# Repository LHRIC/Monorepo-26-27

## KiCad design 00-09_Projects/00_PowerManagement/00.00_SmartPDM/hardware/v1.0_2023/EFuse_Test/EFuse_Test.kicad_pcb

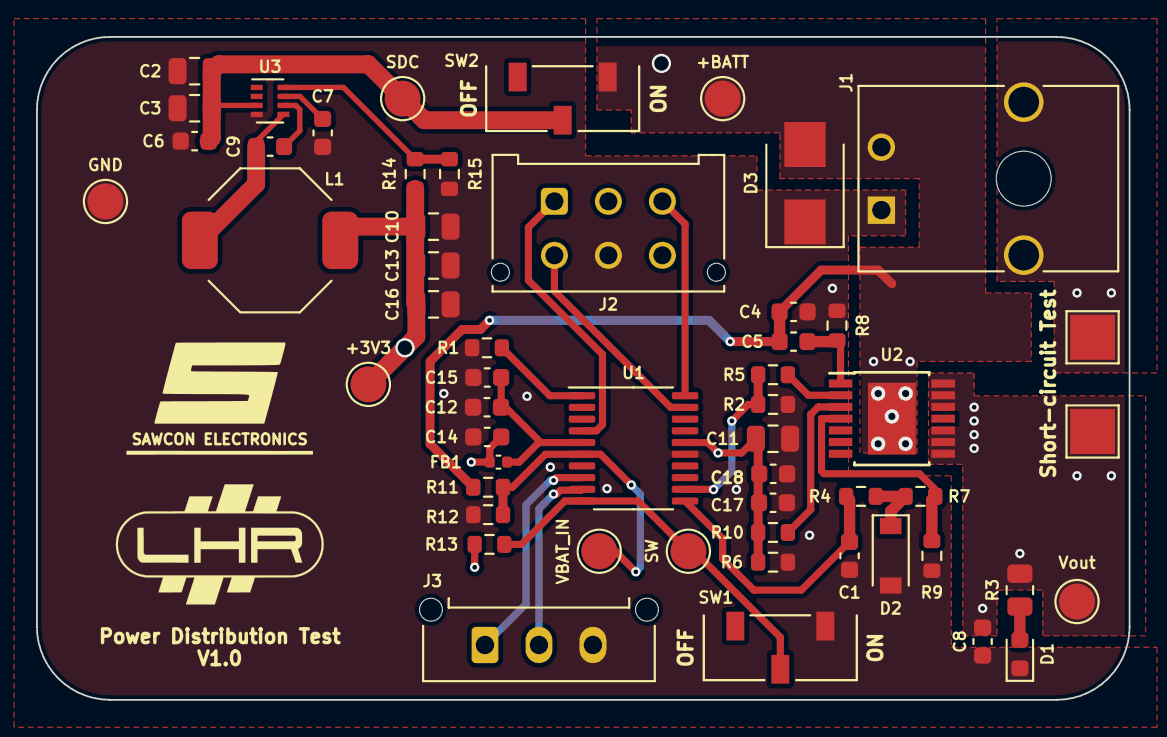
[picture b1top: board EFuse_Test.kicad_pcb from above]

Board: 4 copper layers, 60.7 x 36.8 mm, 53 parts (0 on the bottom side), 26 nets.

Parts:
C1: 220pF; C_0603_1608Metric
C2, C3: 4.7uF; C_0805_2012Metric
C4, C6, C9, C12, C14, C17, C18: .1uF; C_0603_1608Metric
C5: 47nF; C_0603_1608Metric
C7: 33nF; C_0603_1608Metric
C8: 10nF; C_0603_1608Metric
C10, C13, C16: 22uF; C_0805_2012Metric
C11: 10uF; C_0805_2012Metric
C15: 1uF; C_0603_1608Metric
D1: LED; LED_0603_1608Metric
D2: 3.3V; D_SOD-123
D3: 33.2v; D_SMB
FB1: 100 @ 100MHz; C_0402_1005Metric
J1: Conn_01x04; 1723103102
J2: Conn_02x03_Odd_Even; Molex_Micro-Fit_3.0_43045-0612_2x03_P3.00mm_Vertical
J3: Conn_01x03; Molex_Micro-Fit_3.0_43650-0315_1x03_P3.00mm_Vertical
L1: 4.7uH; SRU8043-4R7Y
R1, R2, R6, R13, R15: 10k; R_0603_1608Metric
R3: 1k; R_0805_2012Metric
R4, R5, R7, R10: 4.7k; R_0603_1608Metric
R8: 47; R_0603_1608Metric
R9: 4.42k; R_0603_1608Metric
R11: 16k; R_0603_1608Metric
R12: 3.9k; R_0603_1608Metric
R14: 30.9k; R_0603_1608Metric
SW1, SW2: SW_SPST; SW_JS102011JCQN
TP1, TP2, TP3, TP4, TP5, TP6, TP7: TP; TestPoint_Pad_D2.0mm
U1: STM32F030F4P6TR; TSSOP-20_4.4x6.5mm_P0.65mm
U2: BTS7006-1EPZ; Infineon_PG-TSDSO-14-22
U3: TPS62933; SOT-583

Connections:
+3.3VA: C12.1, C15.1, FB1.2, U1.5 (VDDA)
+3V3: C10.1, C11.1, C13.1, C14.1, C16.1, C17.1, C18.1, FB1.1, J2.2, L1.2, R6.2, R10.2, R13.2, R14.1, TP6.1, U1.16 (VDD)
+BATT: C4.1, C5.1, D3.2 (A2), J1.2, R11.1, SW2.1 (A), TP7.1, U2.15 (VS)
CS: C1.1, R4.1, U1.11 (PA5)
EN: R2.2, R5.2, U1.12 (PA6)
GND: C1.2, C2.2, C3.2, C4.2, C6.2, C7.2, C8.2, C10.2, C11.2, C12.2, C13.2, C14.2, C15.2, C16.2, C17.2, C18.2, D1.1 (K), D2.2 (A), D3.1 (A1), J1.1, J1.3, J1.4, J2.5, J3.3, R1.1, R2.1, R6.1, R8.1, R9.2, R12.2, R15.2, SW1.1 (A), TP2.1, U1.15 (VSS), U3.4 (GND)
NRST: J2.1, U1.4 (NRST)
unnamed: C5.2, R8.2, U2.1 (GND)
unnamed: C7.1, U3.7 (SS)
unnamed: C9.1, L1.1, U3.5 (SW)
unnamed: C9.2, U3.6 (BST)
unnamed: D1.2 (A), R3.2
unnamed: D2.1 (K), R4.2, R7.1
unnamed: R1.2, U1.1 (BOOT0)
unnamed: R5.1, U2.2 (IN)
unnamed: R7.2, R9.1, U2.4 (IS)
unnamed: R10.1, U2.3 (DEN)
unnamed: R14.2, R15.1, U3.8 (FB)
SDC: C2.1, C3.1, C6.1, SW2.2 (B), TP1.1, U3.3 (VIN)
SW: R13.1, SW1.2 (B), TP5.1, U1.10 (PA4)
SWCLK: J2.3, U1.20 (PA14)
SWDIO: J2.4, U1.19 (PA13)
UART_RX: J3.2, U1.9 (PA3)
UART_TX: J3.1, U1.8 (PA2)
VBAT_IN: R11.2, R12.1, TP4.1, U1.6 (PA0)
Vout: C8.1, R3.1, TP3.1, U2.8 (OUT), U2.9 (OUT), U2.10 (OUT), U2.12 (OUT), U2.13 (OUT), U2.14 (OUT)

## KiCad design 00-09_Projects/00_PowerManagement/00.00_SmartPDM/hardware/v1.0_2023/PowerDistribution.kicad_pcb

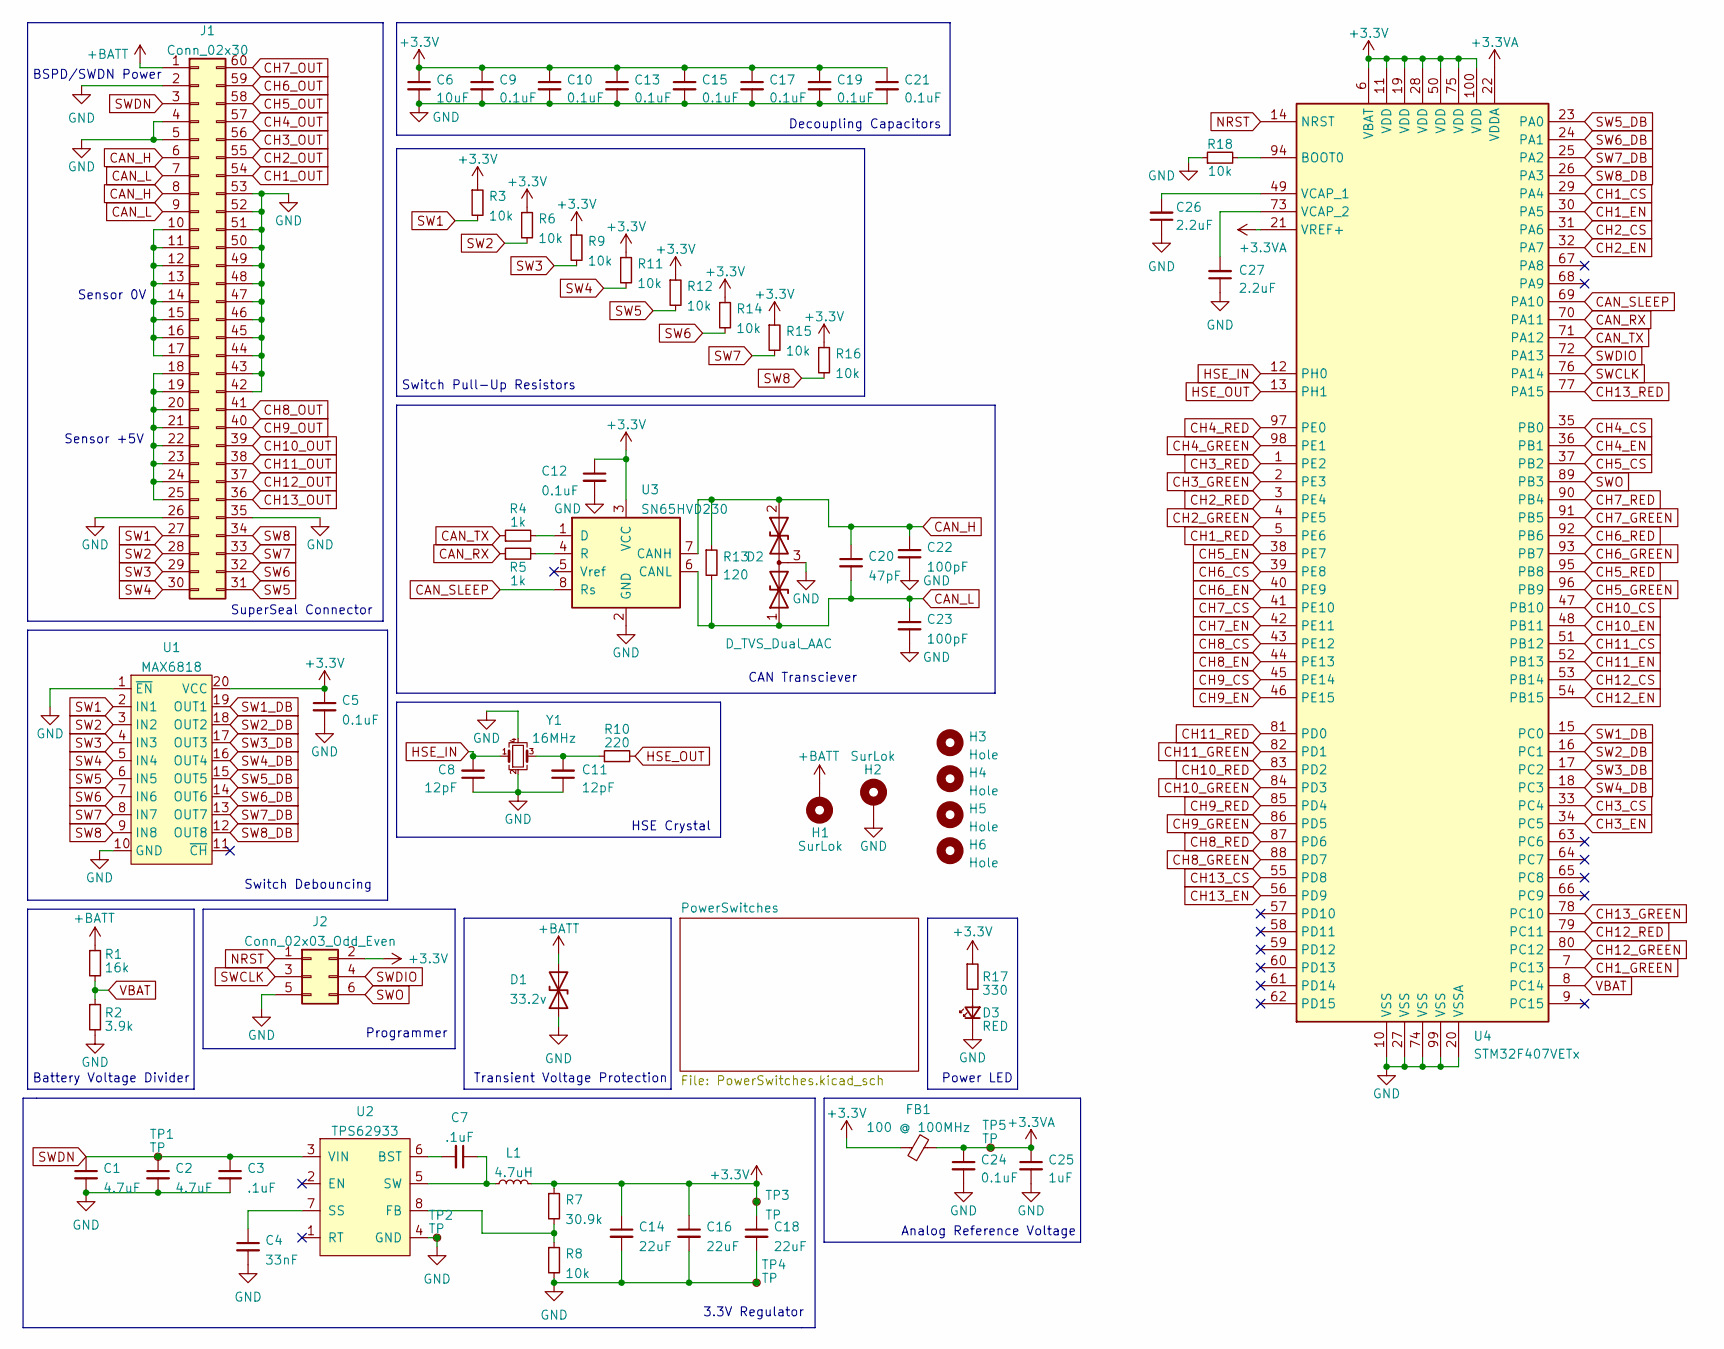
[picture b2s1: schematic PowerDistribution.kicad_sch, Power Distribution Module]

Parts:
C1, C2: 4.7uF; C_0805_2012Metric
C3, C7: .1uF; C_0603_1608Metric
C4: 33nF; C_0603_1608Metric
C5, C9, C10, C12, C13, C15, C17, C19, C21, C24: 0.1uF; C_0603_1608Metric
C6: 10uF; C_0805_2012Metric
C8, C11: 12pF; C_0402_1005Metric
C14, C16, C18: 22uF; C_0805_2012Metric
C20: 47pF; C_0402_1005Metric
C22, C23: 100pF; C_0603_1608Metric
C25: 1uF; C_0603_1608Metric
C26, C27: 2.2uF; C_0603_1608Metric
D1: 33.2v; D_SMB
D2: D_TVS_Dual_AAC; SOT-23
D3: RED; LED_0603_1608Metric
FB1: 100 @ 100MHz; C_0402_1005Metric
H1, H2: SurLok; SurLok_5.7
H3, H4, H5, H6: Hole; MountingHole_3.2mm_M3
J1: Conn_02x30; TE_6473427-1
J2: Conn_02x03_Odd_Even; Molex_Micro-Fit_3.0_43045-0612_2x03_P3.00mm_Vertical
L1: 4.7uH; SRU8043-4R7Y
R1: 16k; R_0603_1608Metric
R2: 3.9k; R_0603_1608Metric
R3, R6, R8, R9, R11, R12, R14, R15, R16, R18: 10k; R_0603_1608Metric
R4, R5: 1k; R_0603_1608Metric
R7: 30.9k; R_0603_1608Metric
R10: 220; R_0603_1608Metric
R13: 120; R_0603_1608Metric
R17: 330; R_0603_1608Metric
TP1, TP2, TP3, TP4, TP5: TP; TestPoint_Pad_D2.0mm
U1: MAX6818; SSOP-20_5.3x7.2mm_P0.65mm
U2: TPS62933; SOT-583
U3: SN65HVD230; SOIC-8_3.9x4.9mm_P1.27mm
U4: STM32F407VETx; LQFP-100_14x14mm_P0.5mm
Y1: 16MHz; Crystal_SMD_3225-4Pin_3.2x2.5mm

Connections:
+3.3VA: C24.1, C25.1, FB1.2, TP5.1, U4.21 (VREF+), U4.22 (VDDA)
+3V3: C5.1, C6.1, C9.1, C10.1, C12.1, C13.1, C14.1, C15.1, C16.1, C17.1, C18.1, C19.1, C21.1, FB1.1, J2.2, L1.2, R3.1, R6.1, R7.1, R9.1, R11.1, R12.1, R14.1, R15.1, R16.1, R17.1, TP3.1, U1.20 (VCC), U3.3 (VCC), U4.6 (VBAT), U4.11 (VDD), U4.19 (VDD), U4.28 (VDD), U4.50 (VDD), U4.75 (VDD), U4.100 (VDD); also elsewhere on the board
+BATT: D1.2 (A2), H1.1, J1.1, R1.1; also elsewhere on the board
CAN_H: C20.1, C22.1, D2.2 (A2), J1.6, J1.8, R13.1, U3.7 (CANH)
CAN_L: C20.2, C23.1, D2.1 (A1), J1.7, J1.9, R13.2, U3.6 (CANL)
CAN_RX: R5.1, U4.70 (PA11)
CAN_SLEEP: U3.8 (Rs), U4.69 (PA10)
CAN_TX: R4.1, U4.71 (PA12)
CH1_CS: U4.29 (PA4); also elsewhere on the board
CH1_EN: U4.30 (PA5); also elsewhere on the board
CH1_GREEN: U4.7 (PC13); also elsewhere on the board
CH1_OUT: J1.54; also elsewhere on the board
CH1_RED: U4.5 (PE6); also elsewhere on the board
CH2_CS: U4.31 (PA6); also elsewhere on the board
CH2_EN: U4.32 (PA7); also elsewhere on the board
CH2_GREEN: U4.4 (PE5); also elsewhere on the board
CH2_OUT: J1.55; also elsewhere on the board
CH2_RED: U4.3 (PE4); also elsewhere on the board
CH3_CS: U4.33 (PC4); also elsewhere on the board
CH3_EN: U4.34 (PC5); also elsewhere on the board
CH3_GREEN: U4.2 (PE3); also elsewhere on the board
CH3_OUT: J1.56; also elsewhere on the board
CH3_RED: U4.1 (PE2); also elsewhere on the board
CH4_CS: U4.35 (PB0); also elsewhere on the board
CH4_EN: U4.36 (PB1); also elsewhere on the board
CH4_GREEN: U4.98 (PE1); also elsewhere on the board
CH4_OUT: J1.57; also elsewhere on the board
CH4_RED: U4.97 (PE0); also elsewhere on the board
CH5_CS: U4.37 (PB2); also elsewhere on the board
CH5_EN: U4.38 (PE7); also elsewhere on the board
CH5_GREEN: U4.96 (PB9); also elsewhere on the board
CH5_OUT: J1.58; also elsewhere on the board
CH5_RED: U4.95 (PB8); also elsewhere on the board
CH6_CS: U4.39 (PE8); also elsewhere on the board
CH6_EN: U4.40 (PE9); also elsewhere on the board
CH6_GREEN: U4.93 (PB7); also elsewhere on the board
CH6_OUT: J1.59; also elsewhere on the board
CH6_RED: U4.92 (PB6); also elsewhere on the board
CH7_CS: U4.41 (PE10); also elsewhere on the board
CH7_EN: U4.42 (PE11); also elsewhere on the board
CH7_GREEN: U4.91 (PB5); also elsewhere on the board
CH7_OUT: J1.60; also elsewhere on the board
CH7_RED: U4.90 (PB4); also elsewhere on the board
CH8_CS: U4.43 (PE12); also elsewhere on the board
CH8_EN: U4.44 (PE13); also elsewhere on the board
CH8_GREEN: U4.88 (PD7); also elsewhere on the board
CH8_OUT: J1.41; also elsewhere on the board
CH8_RED: U4.87 (PD6); also elsewhere on the board
CH9_CS: U4.45 (PE14); also elsewhere on the board
CH9_EN: U4.46 (PE15); also elsewhere on the board
CH9_GREEN: U4.86 (PD5); also elsewhere on the board
CH9_OUT: J1.40; also elsewhere on the board
CH9_RED: U4.85 (PD4); also elsewhere on the board
CH10_CS: U4.47 (PB10); also elsewhere on the board
CH10_EN: U4.48 (PB11); also elsewhere on the board
CH10_GREEN: U4.84 (PD3); also elsewhere on the board
CH10_OUT: J1.39; also elsewhere on the board
CH10_RED: U4.83 (PD2); also elsewhere on the board
CH11_CS: U4.51 (PB12); also elsewhere on the board
CH11_EN: U4.52 (PB13); also elsewhere on the board
CH11_GREEN: U4.82 (PD1); also elsewhere on the board
CH11_OUT: J1.38; also elsewhere on the board
CH11_RED: U4.81 (PD0); also elsewhere on the board
CH12_CS: U4.53 (PB14); also elsewhere on the board
CH12_EN: U4.54 (PB15); also elsewhere on the board
CH12_GREEN: U4.80 (PC12); also elsewhere on the board
CH12_OUT: J1.37; also elsewhere on the board
CH12_RED: U4.79 (PC11); also elsewhere on the board
CH13_CS: U4.55 (PD8); also elsewhere on the board
CH13_EN: U4.56 (PD9); also elsewhere on the board
CH13_GREEN: U4.78 (PC10); also elsewhere on the board
CH13_OUT: J1.36; also elsewhere on the board
CH13_RED: U4.77 (PA15); also elsewhere on the board
GND: C1.2, C2.2, C3.2, C4.2, C5.2, C6.2, C8.1, C9.2, C10.2, C11.1, C12.2, C13.2, C14.2, C15.2, C16.2, C17.2, C18.2, C19.2, C21.2, C22.2, C23.2, C24.2, C25.2, C26.1, C27.1, D1.1 (A1), D2.3 (common), D3.1 (K), H2.1, J1.2, J1.4, J1.5, J1.26, J1.35, J1.42, J1.43, J1.44, J1.45, J1.46, J1.47, J1.48, J1.49, J1.50, J1.51, J1.52, J1.53, J2.5, R2.2, R8.2, R18.1, TP2.1, TP4.1, U1.1 (~EN), U1.10 (GND), U2.4 (GND), U3.2 (GND), U4.10 (VSS), U4.20 (VSSA), U4.27 (VSS), U4.74 (VSS), U4.99 (VSS), Y1.2, Y1.4; also elsewhere on the board
HSE_IN: C8.2, U4.12 (PH0), Y1.1
HSE_OUT: R10.2, U4.13 (PH1)
NRST: J2.1, U4.14 (NRST)
unnamed: C4.1, U2.7 (SS)
unnamed: C7.1, L1.1, U2.5 (SW)
unnamed: C7.2, U2.6 (BST)
unnamed: C11.2, R10.1, Y1.3
unnamed: C26.2, U4.49 (VCAP_1)
unnamed: C27.2, U4.73 (VCAP_2)
unnamed: D3.2 (A), R17.2
unnamed: J1.10, J1.11, J1.12, J1.13, J1.14, J1.15, J1.16, J1.17
unnamed: J1.18, J1.19, J1.20, J1.21, J1.22, J1.23, J1.24, J1.25
unnamed: R4.2, U3.1 (D)
unnamed: R5.2, U3.4 (R)
unnamed: R7.2, R8.1, U2.8 (FB)
unnamed: R18.2, U4.94 (BOOT0)
SW1: J1.27, R3.2, U1.2 (IN1)
SW1_DB: U1.19 (OUT1), U4.15 (PC0)
SW2: J1.28, R6.2, U1.3 (IN2)
SW2_DB: U1.18 (OUT2), U4.16 (PC1)
SW3: J1.29, R9.2, U1.4 (IN3)
SW3_DB: U1.17 (OUT3), U4.17 (PC2)
SW4: J1.30, R11.2, U1.5 (IN4)
SW4_DB: U1.16 (OUT4), U4.18 (PC3)
SW5: J1.31, R12.2, U1.6 (IN5)
SW5_DB: U1.15 (OUT5), U4.23 (PA0)
SW6: J1.32, R14.2, U1.7 (IN6)
SW6_DB: U1.14 (OUT6), U4.24 (PA1)
SW7: J1.33, R15.2, U1.8 (IN7)
SW7_DB: U1.13 (OUT7), U4.25 (PA2)
SW8: J1.34, R16.2, U1.9 (IN8)
SW8_DB: U1.12 (OUT8), U4.26 (PA3)
SWCLK: J2.3, U4.76 (PA14)
SWDIO: J2.4, U4.72 (PA13)
SWDN: C1.1, C2.1, C3.1, J1.3, TP1.1, U2.3 (VIN)
SWO: J2.6, U4.89 (PB3)
VBAT: R1.2, R2.1, U4.8 (PC14)

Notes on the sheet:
Decoupling Capacitors
SuperSeal Connector
Switch Debouncing
Analog Reference Voltage
Power LED
Programmer
CAN Transciever
Sensor +5V
Sensor 0V
Transient Voltage Protection
3.3V Regulator
Battery Voltage Divider
HSE Crystal
BSPD/SWDN Power
Switch Pull-Up Resistors

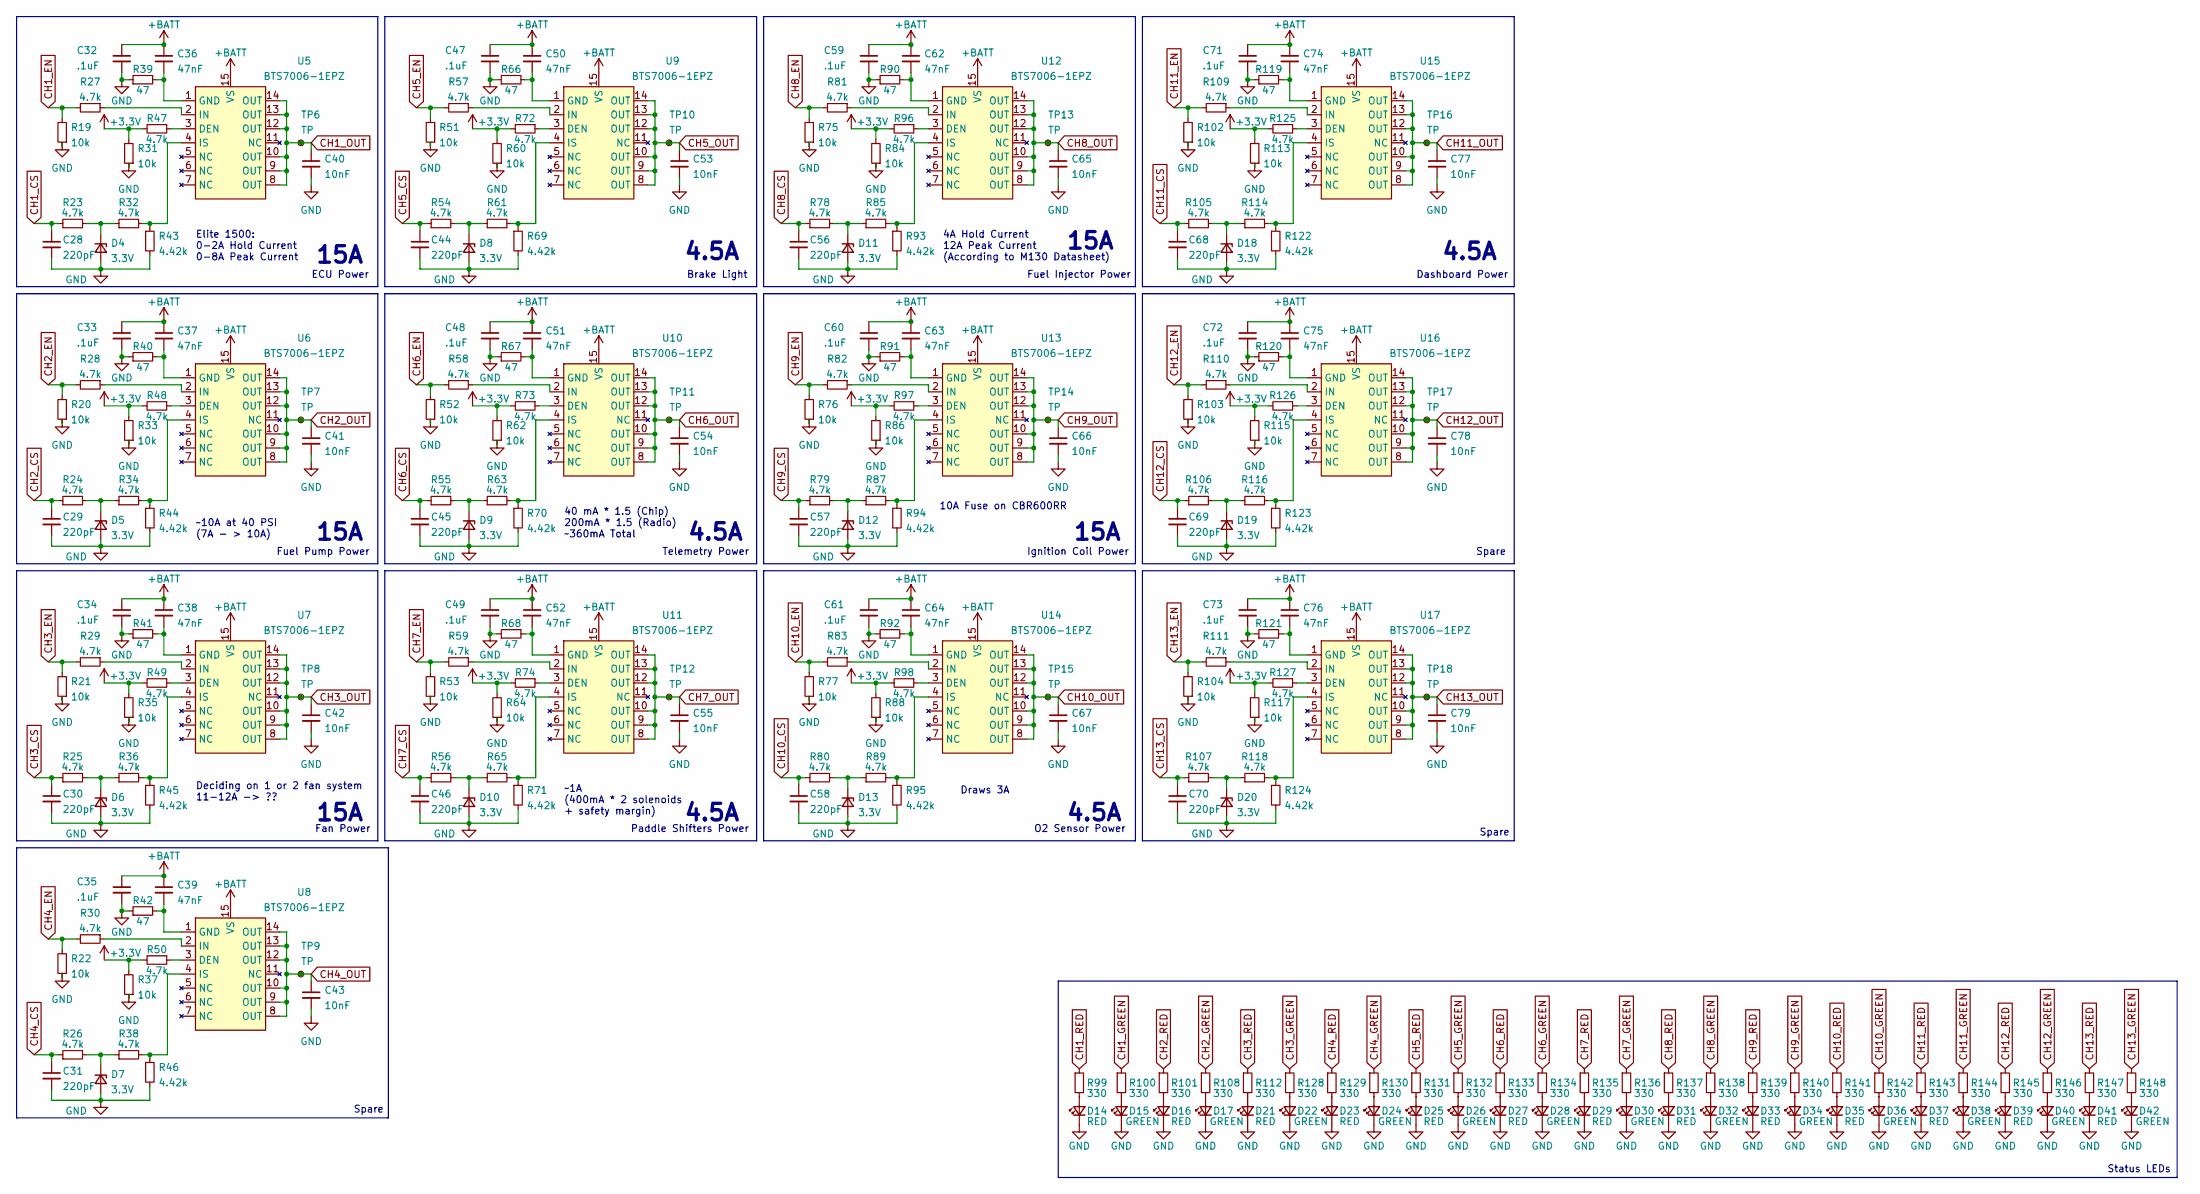
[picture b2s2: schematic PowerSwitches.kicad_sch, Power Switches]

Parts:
C28, C29, C30, C31, C44, C45, C46, C56, C57, C58, C68, C69, C70: 220pF; C_0603_1608Metric
C32, C33, C34, C35, C47, C48, C49, C59, C60, C61, C71, C72, C73: .1uF; C_0603_1608Metric
C36, C37, C38, C39, C50, C51, C52, C62, C63, C64, C74, C75, C76: 47nF; C_0603_1608Metric
C40, C41, C42, C43, C53, C54, C55, C65, C66, C67, C77, C78, C79: 10nF; C_0603_1608Metric
D4, D5, D6, D7, D8, D9, D10, D11, D12, D13, D18, D19, D20: 3.3V; D_SOD-123
D14, D16, D21, D23, D25, D27, D29, D31, D33, D35, D37, D39, D41: RED; LED_0603_1608Metric
D15, D17, D22, D24, D26, D28, D30, D32, D34, D36, D38, D40, D42: GREEN; LED_0603_1608Metric
R19, R20, R21, R22, R31, R33, R35, R37, R51, R52, R53, R60, R62, R64, R75, R76, R77, R84, R86, R88, R102, R103, R104, R113, R115, R117: 10k; R_0603_1608Metric
R23, R24, R25, R26, R27, R28, R29, R30, R32, R34, R36, R38, R47, R48, R49, R50, R54, R55, R56, R57, R58, R59, R61, R63, R65, R72, R73, R74, R78, R79, R80, R81, R82, R83, R85, R87, R89, R96, R97, R98, R105, R106, R107, R109, R110, R111, R114, R116, R118, R125, R126, R127: 4.7k; R_0603_1608Metric
R39, R40, R41, R42, R66, R67, R68, R90, R91, R92, R119, R120, R121: 47; R_0603_1608Metric
R43, R44, R45, R46, R69, R70, R71, R93, R94, R95, R122, R123, R124: 4.42k; R_0603_1608Metric
R99, R100, R101, R108, R112, R128, R129, R130, R131, R132, R133, R134, R135, R136, R137, R138, R139, R140, R141, R142, R143, R144, R145, R146, R147, R148: 330; R_0603_1608Metric
TP6, TP7, TP8, TP9, TP10, TP11, TP12, TP13, TP14, TP15, TP16, TP17, TP18: TP; TestPoint_Pad_D2.0mm
U5, U6, U7, U8, U9, U10, U11, U12, U13, U14, U15, U16, U17: BTS7006-1EPZ; Infineon_PG-TSDSO-14-22

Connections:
+3V3: R31.2, R33.2, R35.2, R37.2, R47.2, R48.2, R49.2, R50.2, R60.2, R62.2, R64.2, R72.2, R73.2, R74.2, R84.2, R86.2, R88.2, R96.2, R97.2, R98.2, R113.2, R115.2, R117.2, R125.2, R126.2, R127.2; also elsewhere on the board
+BATT: C32.1, C33.1, C34.1, C35.1, C36.1, C37.1, C38.1, C39.1, C47.1, C48.1, C49.1, C50.1, C51.1, C52.1, C59.1, C60.1, C61.1, C62.1, C63.1, C64.1, C71.1, C72.1, C73.1, C74.1, C75.1, C76.1, U5.15 (VS), U6.15 (VS), U7.15 (VS), U8.15 (VS), U9.15 (VS), U10.15 (VS), U11.15 (VS), U12.15 (VS), U13.15 (VS), U14.15 (VS), U15.15 (VS), U16.15 (VS), U17.15 (VS); also elsewhere on the board
CH1_CS: C28.1, R23.1; also elsewhere on the board
CH1_EN: R19.2, R27.2; also elsewhere on the board
CH1_GREEN: R100.1; also elsewhere on the board
CH1_OUT: C40.1, TP6.1, U5.8 (OUT), U5.9 (OUT), U5.10 (OUT), U5.12 (OUT), U5.13 (OUT), U5.14 (OUT); also elsewhere on the board
CH1_RED: R99.1; also elsewhere on the board
CH2_CS: C29.1, R24.1; also elsewhere on the board
CH2_EN: R20.2, R28.2; also elsewhere on the board
CH2_GREEN: R108.1; also elsewhere on the board
CH2_OUT: C41.1, TP7.1, U6.8 (OUT), U6.9 (OUT), U6.10 (OUT), U6.12 (OUT), U6.13 (OUT), U6.14 (OUT); also elsewhere on the board
CH2_RED: R101.1; also elsewhere on the board
CH3_CS: C30.1, R25.1; also elsewhere on the board
CH3_EN: R21.2, R29.2; also elsewhere on the board
CH3_GREEN: R128.1; also elsewhere on the board
CH3_OUT: C42.1, TP8.1, U7.8 (OUT), U7.9 (OUT), U7.10 (OUT), U7.12 (OUT), U7.13 (OUT), U7.14 (OUT); also elsewhere on the board
CH3_RED: R112.1; also elsewhere on the board
CH4_CS: C31.1, R26.1; also elsewhere on the board
CH4_EN: R22.2, R30.2; also elsewhere on the board
CH4_GREEN: R130.1; also elsewhere on the board
CH4_OUT: C43.1, TP9.1, U8.8 (OUT), U8.9 (OUT), U8.10 (OUT), U8.12 (OUT), U8.13 (OUT), U8.14 (OUT); also elsewhere on the board
CH4_RED: R129.1; also elsewhere on the board
CH5_CS: C44.1, R54.1; also elsewhere on the board
CH5_EN: R51.2, R57.2; also elsewhere on the board
CH5_GREEN: R132.1; also elsewhere on the board
CH5_OUT: C53.1, TP10.1, U9.8 (OUT), U9.9 (OUT), U9.10 (OUT), U9.12 (OUT), U9.13 (OUT), U9.14 (OUT); also elsewhere on the board
CH5_RED: R131.1; also elsewhere on the board
CH6_CS: C45.1, R55.1; also elsewhere on the board
CH6_EN: R52.2, R58.2; also elsewhere on the board
CH6_GREEN: R134.1; also elsewhere on the board
CH6_OUT: C54.1, TP11.1, U10.8 (OUT), U10.9 (OUT), U10.10 (OUT), U10.12 (OUT), U10.13 (OUT), U10.14 (OUT); also elsewhere on the board
CH6_RED: R133.1; also elsewhere on the board
CH7_CS: C46.1, R56.1; also elsewhere on the board
CH7_EN: R53.2, R59.2; also elsewhere on the board
CH7_GREEN: R136.1; also elsewhere on the board
CH7_OUT: C55.1, TP12.1, U11.8 (OUT), U11.9 (OUT), U11.10 (OUT), U11.12 (OUT), U11.13 (OUT), U11.14 (OUT); also elsewhere on the board
CH7_RED: R135.1; also elsewhere on the board
CH8_CS: C56.1, R78.1; also elsewhere on the board
CH8_EN: R75.2, R81.2; also elsewhere on the board
CH8_GREEN: R138.1; also elsewhere on the board
CH8_OUT: C65.1, TP13.1, U12.8 (OUT), U12.9 (OUT), U12.10 (OUT), U12.12 (OUT), U12.13 (OUT), U12.14 (OUT); also elsewhere on the board
CH8_RED: R137.1; also elsewhere on the board
CH9_CS: C57.1, R79.1; also elsewhere on the board
CH9_EN: R76.2, R82.2; also elsewhere on the board
CH9_GREEN: R140.1; also elsewhere on the board
CH9_OUT: C66.1, TP14.1, U13.8 (OUT), U13.9 (OUT), U13.10 (OUT), U13.12 (OUT), U13.13 (OUT), U13.14 (OUT); also elsewhere on the board
CH9_RED: R139.1; also elsewhere on the board
CH10_CS: C58.1, R80.1; also elsewhere on the board
CH10_EN: R77.2, R83.2; also elsewhere on the board
CH10_GREEN: R142.1; also elsewhere on the board
CH10_OUT: C67.1, TP15.1, U14.8 (OUT), U14.9 (OUT), U14.10 (OUT), U14.12 (OUT), U14.13 (OUT), U14.14 (OUT); also elsewhere on the board
CH10_RED: R141.1; also elsewhere on the board
CH11_CS: C68.1, R105.1; also elsewhere on the board
CH11_EN: R102.2, R109.2; also elsewhere on the board
CH11_GREEN: R144.1; also elsewhere on the board
CH11_OUT: C77.1, TP16.1, U15.8 (OUT), U15.9 (OUT), U15.10 (OUT), U15.12 (OUT), U15.13 (OUT), U15.14 (OUT); also elsewhere on the board
CH11_RED: R143.1; also elsewhere on the board
CH12_CS: C69.1, R106.1; also elsewhere on the board
CH12_EN: R103.2, R110.2; also elsewhere on the board
CH12_GREEN: R146.1; also elsewhere on the board
CH12_OUT: C78.1, TP17.1, U16.8 (OUT), U16.9 (OUT), U16.10 (OUT), U16.12 (OUT), U16.13 (OUT), U16.14 (OUT); also elsewhere on the board
CH12_RED: R145.1; also elsewhere on the board
CH13_CS: C70.1, R107.1; also elsewhere on the board
CH13_EN: R104.2, R111.2; also elsewhere on the board
CH13_GREEN: R148.1; also elsewhere on the board
CH13_OUT: C79.1, TP18.1, U17.8 (OUT), U17.9 (OUT), U17.10 (OUT), U17.12 (OUT), U17.13 (OUT), U17.14 (OUT); also elsewhere on the board
CH13_RED: R147.1; also elsewhere on the board
GND: C28.2, C29.2, C30.2, C31.2, C32.2, C33.2, C34.2, C35.2, C40.2, C41.2, C42.2, C43.2, C44.2, C45.2, C46.2, C47.2, C48.2, C49.2, C53.2, C54.2, C55.2, C56.2, C57.2, C58.2, C59.2, C60.2, C61.2, C65.2, C66.2, C67.2, C68.2, C69.2, C70.2, C71.2, C72.2, C73.2, C77.2, C78.2, C79.2, D4.2 (A), D5.2 (A), D6.2 (A), D7.2 (A), D8.2 (A), D9.2 (A), D10.2 (A), D11.2 (A), D12.2 (A), D13.2 (A), D14.1 (K), D15.1 (K), D16.1 (K), D17.1 (K), D18.2 (A), D19.2 (A), D20.2 (A), D21.1 (K), D22.1 (K), D23.1 (K), D24.1 (K), D25.1 (K), D26.1 (K), D27.1 (K), D28.1 (K), D29.1 (K), D30.1 (K), D31.1 (K), D32.1 (K), D33.1 (K), D34.1 (K), D35.1 (K), D36.1 (K), D37.1 (K), D38.1 (K), D39.1 (K), D40.1 (K), D41.1 (K), D42.1 (K), R19.1, R20.1, R21.1, R22.1, R31.1, R33.1, R35.1, R37.1, R39.1, R40.1, R41.1, R42.1, R43.2, R44.2, R45.2, R46.2, R51.1, R52.1, R53.1, R60.1, R62.1, R64.1, R66.1, R67.1, R68.1, R69.2, R70.2, R71.2, R75.1, R76.1, R77.1, R84.1, R86.1, R88.1, R90.1, R91.1, R92.1, R93.2, R94.2, R95.2, R102.1, R103.1, R104.1, R113.1, R115.1, R117.1, R119.1, R120.1, R121.1, R122.2, R123.2, R124.2; also elsewhere on the board
unnamed: C36.2, R39.2, U5.1 (GND)
unnamed: C37.2, R40.2, U6.1 (GND)
unnamed: C38.2, R41.2, U7.1 (GND)
unnamed: C39.2, R42.2, U8.1 (GND)
unnamed: C50.2, R66.2, U9.1 (GND)
unnamed: C51.2, R67.2, U10.1 (GND)
unnamed: C52.2, R68.2, U11.1 (GND)
unnamed: C62.2, R90.2, U12.1 (GND)
unnamed: C63.2, R91.2, U13.1 (GND)
unnamed: C64.2, R92.2, U14.1 (GND)
unnamed: C74.2, R119.2, U15.1 (GND)
unnamed: C75.2, R120.2, U16.1 (GND)
unnamed: C76.2, R121.2, U17.1 (GND)
unnamed: D4.1 (K), R23.2, R32.1
unnamed: D5.1 (K), R24.2, R34.1
unnamed: D6.1 (K), R25.2, R36.1
unnamed: D7.1 (K), R26.2, R38.1
unnamed: D8.1 (K), R54.2, R61.1
unnamed: D9.1 (K), R55.2, R63.1
unnamed: D10.1 (K), R56.2, R65.1
unnamed: D11.1 (K), R78.2, R85.1
unnamed: D12.1 (K), R79.2, R87.1
unnamed: D13.1 (K), R80.2, R89.1
unnamed: D14.2 (A), R99.2
unnamed: D15.2 (A), R100.2
unnamed: D16.2 (A), R101.2
unnamed: D17.2 (A), R108.2
unnamed: D18.1 (K), R105.2, R114.1
unnamed: D19.1 (K), R106.2, R116.1
unnamed: D20.1 (K), R107.2, R118.1
unnamed: D21.2 (A), R112.2
unnamed: D22.2 (A), R128.2
unnamed: D23.2 (A), R129.2
unnamed: D24.2 (A), R130.2
unnamed: D25.2 (A), R131.2
unnamed: D26.2 (A), R132.2
unnamed: D27.2 (A), R133.2
unnamed: D28.2 (A), R134.2
unnamed: D29.2 (A), R135.2
unnamed: D30.2 (A), R136.2
unnamed: D31.2 (A), R137.2
unnamed: D32.2 (A), R138.2
unnamed: D33.2 (A), R139.2
unnamed: D34.2 (A), R140.2
unnamed: D35.2 (A), R141.2
unnamed: D36.2 (A), R142.2
unnamed: D37.2 (A), R143.2
unnamed: D38.2 (A), R144.2
unnamed: D39.2 (A), R145.2
unnamed: D40.2 (A), R146.2
unnamed: D41.2 (A), R147.2
unnamed: D42.2 (A), R148.2
unnamed: R27.1, U5.2 (IN)
unnamed: R28.1, U6.2 (IN)
unnamed: R29.1, U7.2 (IN)
unnamed: R30.1, U8.2 (IN)
unnamed: R32.2, R43.1, U5.4 (IS)
unnamed: R34.2, R44.1, U6.4 (IS)
unnamed: R36.2, R45.1, U7.4 (IS)
unnamed: R38.2, R46.1, U8.4 (IS)
unnamed: R47.1, U5.3 (DEN)
unnamed: R48.1, U6.3 (DEN)
unnamed: R49.1, U7.3 (DEN)
unnamed: R50.1, U8.3 (DEN)
unnamed: R57.1, U9.2 (IN)
unnamed: R58.1, U10.2 (IN)
unnamed: R59.1, U11.2 (IN)
unnamed: R61.2, R69.1, U9.4 (IS)
unnamed: R63.2, R70.1, U10.4 (IS)
unnamed: R65.2, R71.1, U11.4 (IS)
unnamed: R72.1, U9.3 (DEN)
unnamed: R73.1, U10.3 (DEN)
unnamed: R74.1, U11.3 (DEN)
unnamed: R81.1, U12.2 (IN)
unnamed: R82.1, U13.2 (IN)
unnamed: R83.1, U14.2 (IN)
unnamed: R85.2, R93.1, U12.4 (IS)
unnamed: R87.2, R94.1, U13.4 (IS)
unnamed: R89.2, R95.1, U14.4 (IS)
unnamed: R96.1, U12.3 (DEN)
unnamed: R97.1, U13.3 (DEN)
unnamed: R98.1, U14.3 (DEN)
unnamed: R109.1, U15.2 (IN)
unnamed: R110.1, U16.2 (IN)
unnamed: R111.1, U17.2 (IN)
unnamed: R114.2, R122.1, U15.4 (IS)
unnamed: R116.2, R123.1, U16.4 (IS)
unnamed: R118.2, R124.1, U17.4 (IS)
unnamed: R125.1, U15.3 (DEN)
unnamed: R126.1, U16.3 (DEN)
unnamed: R127.1, U17.3 (DEN)

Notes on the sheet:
ECU Power
Deciding on 1 or 2 fan system 11-12A -> ??
~1A (400mA * 2 solenoids + safety margin)
Status LEDs
4.5A
Elite 1500: 0-2A Hold Current 0-8A Peak Current
Spare
Telemetry Power
15A
Brake Light
O2 Sensor Power
Fan Power
Fuel Injector Power
40 mA * 1.5 (Chip) 200mA * 1.5 (Radio) ~360mA Total
Dashboard Power
4A Hold Current 12A Peak Current (According to M130 Datasheet)
Fuel Pump Power
Ignition Coil Power
10A Fuse on CBR600RR
Draws 3A
~10A at 40 PSI (7A - > 10A)
Paddle Shifters Power

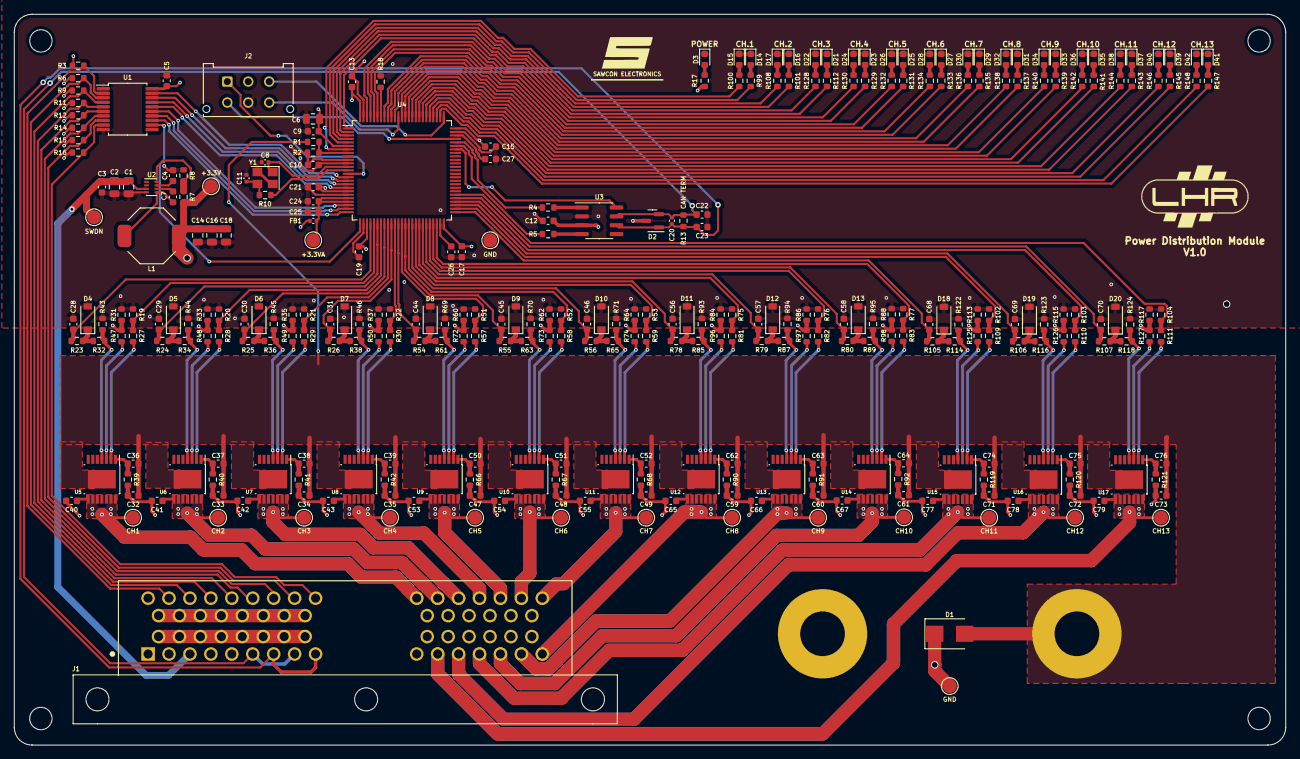
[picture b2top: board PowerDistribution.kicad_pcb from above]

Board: 4 copper layers, 182.2 x 104.7 mm, 315 parts (0 on the bottom side), 202 nets.

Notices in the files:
parts and their libraries:
Copyright 2021 Accelerated Designs. All rights reserved.
